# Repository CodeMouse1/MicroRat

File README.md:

# MicroRat: Eine technische Dokumentation

<div align="center">

<div align="left">

Dieses Repository dokumentiert und bündelt das Projekt MicroRat – eine an der Micromouse orientierte Plattform für Studierenden der BHT.
Es stellt ein vollständiges Paket aus Hardware und Software-Komponenten bereit und soll als Grundlage für eigene Projekte, Experimente und Weiterentwicklungen dienen.
<div align="center">
	
<div align="left">
<br>
Wenn der Begriff einer Micromouse unbekannt ist findet man unter diesem Link ein Erläuterungsvideo:
[▶️](https://www.youtube.com/watch?v=ZMQbHMgK2rw)
<br>

## Technische Beschreibung
Micromouse ist ein internationaler Robotik-Wettbewerb, bei dem kleine, autonome Roboter ein Labyrinth selbstständig erkunden und den schnellsten Weg zum Ziel finden müssen.
Die Fahrzeuge agieren vollkommen ohne externe Hilfe und entscheiden selbstständig, wie sie Hindernisse und Wände erkennen.

_Die MicroRat soll als Einstieg in diese Thematik dienen._

**Hardware Umsetzung**

Das Aussehen einer Micromouse hängt stark vom jeweiligen Erbauer ab. Die MicroRat ist bewusst so gestaltet, dass sie grundlegende Funktionen mit einfacher Benutzbarkeit und Programmierbarkeit kombiniert.
Zur Umgebungserfassung kommen folgende Sensoren zum Einsatz:
###### Sensorik
- SHARP Infrarot-Sensoren, jeweils im 90°-Winkel senkrecht zu den Wänden montiert
- HC-SR04 Ultraschall-Sensor an der Vorderseite

###### Antrieb
- DC-Motoren mit Encodern für Antrieb und Drehzahlerfassung 

###### Stromversorgung
- 2s1p Li-Ion Akkupack für stabile Energieversorgung  

###### Steuerung & Schnittstellen

- XMC-1402 Mikrocontroller, programmierbar über Debug-Connector
- UART Schnittstelle zur Ausgabe der Sensordaten 

<div align="center">

Hier ein Link zu einer 3D Ansicht: [3D-Modell](https://a360.co/3VB2RBQ)
<div align="left">
<br>

**Software-Architektur**

Die MicroRat wird über den XMC-1402 Mikrocontroller gesteuert, der Sensoren ausliest, Motoren ansteuert und die Labyrinthnavigation übernimmt.

###### Entwicklungsumgebung
- **Sprache:** C
- **IDE:** DAVE™ 
- **Debugging:** Über den Debug-Connector des XMC4500

###### Hauptfunktionen
- **Sensordaten-Auswertung:** IR- und Ultraschallsensor erkennen Wände und Hindernisse
- **Motorsteuerung:** Drehzahlgeregelte Ansteuerung der DC-Motoren mittels PD-Regler
- **Labyrinth-Algorithmus:**
	- Wandfolger (links/rechts), kartografiert
	- Floodfill, Optimierung des schnellsten Weges zum Ziel
- **Kommunikation:** Sensordaten über UART für Debugging & Logging
<div align="center">

<div align="left">

## Verwendung von KiCad 8.0
<div align="center">
	
<div align="left">
Für dieses Projekt haben wir KiCad 8.0 gewählt aus folgenden Gründen:
<br/><br/>

- **Fortschrittliche Funktionen:** Bietet erweiterte Tools für Schaltplanerstellung und Leiterplattendesign.
- **Open-Source-Software:** Kostenfrei und kontinuierlich verbessert durch eine große Community.
- **Plattformübergreifende Unterstützung:** Ermöglicht nahtlose Zusammenarbeit unabhängig vom Betriebssystem.

- **Kompatibilität und Exportmöglichkeiten:** Unterstützt viele Dateiformate und erleichtert die Integration mit anderen Tools.

Für eine grundlegende Einführung in KiCad bitte dieser Ratte folgen: [🐀](https://docs.kicad.org/)

## Anleitung

### Dave IDE 
<div align="center">
	
<div align="left">
<br>

DAVE IDE (Digital Application Virtual Engineering) ist eine benutzerfreundliche Entwicklungsumgebung für Mikrocontroller und eingebettete Systeme. Sie bietet Programmierung, Debugging und Analyse in einer Plattform.

###### Hauptfunktionen:

- **Projektverwaltung:** Projekte erstellen, importieren und konfigurieren.
- **Code-Editor:** Syntax-Highlighting, App-Help und Fehlererkennung.
- **Debugging:** Breakpoints setzen, Schritt-für-Schritt-Debugging, Variablen überwachen.

##### Erste Schritte mit DAVE IDE
- **Installation:**[⬇️](https://softwaretools.infineon.com/tools/com.ifx.tb.tool.daveide)
- **Projekt importieren:** Datei → Importieren → ZIP auswählen.

### Micromouse Simulator
<div align="center">
	
<div align="left">
<br>
Zum einfachen Testen und Erproben von Micromouse-Software ohne physische Hardware wird die Nutzung des MMS-Simulators empfohlen, mit dem Labyrinthe virtuell erstellt und Algorithmen sicher ausprobiert werden können: [Micromouse Simulator](https://github.com/mackorone/mms)

## Lizenzinformationen
Dieses Projekt ist Lizensiert unter der CC 4.0 Lizenz
https://creativecommons.org/licenses/by/4.0/

## Mitwirken
Wir freuen uns auf eure Erweiterungen! Wenn du an diesem Projekt mitarbeiten möchtest, folge bitte diesen Schritten:

1. **Fork dieses Repository**: Klicke oben rechts auf die Schaltfläche "Fork", um eine Kopie des Repositories in deinem GitLab-Konto zu erstellen.

2. **Clone das Forked Repository**: Klone dein geforktes Repository auf deinen lokalen Rechner.
    ```bash
    git clone https://github.com/dein-username/dein-repository.git
    ```

3. **Erstelle einen neuen Branch**: Erstelle einen neuen Branch für deine Arbeit.
    ```bash
    git checkout -b mein-neuer-branch
    ```

4. **Nimm deine Änderungen vor**: Führe die gewünschten Änderungen durch und committe sie.
    ```bash
    git add .
    git commit -m "Beschreibe deine Änderungen"
    ```

5. **Push deine Änderungen**: Push deine Änderungen zu deinem Fork.
    ```bash
    git push origin mein-neuer-branch
    ```

6. **Erstelle einen Pull Request**: Gehe zu deinem geforkten Repository auf GitLab und klicke auf die Schaltfläche "New Pull Request", um deine Änderungen zur Überprüfung einzureichen.

## Entwickler

Hardware & Software: Marcus Stake Alvarado

Ursprüngliches Hardware-Design: Nico Hinrichs

Ansprechprofessor: Prof. Dipl.-Ing. Koshan Mahdi

<div align="center">

**Viel Spaß mit der MicroRat**

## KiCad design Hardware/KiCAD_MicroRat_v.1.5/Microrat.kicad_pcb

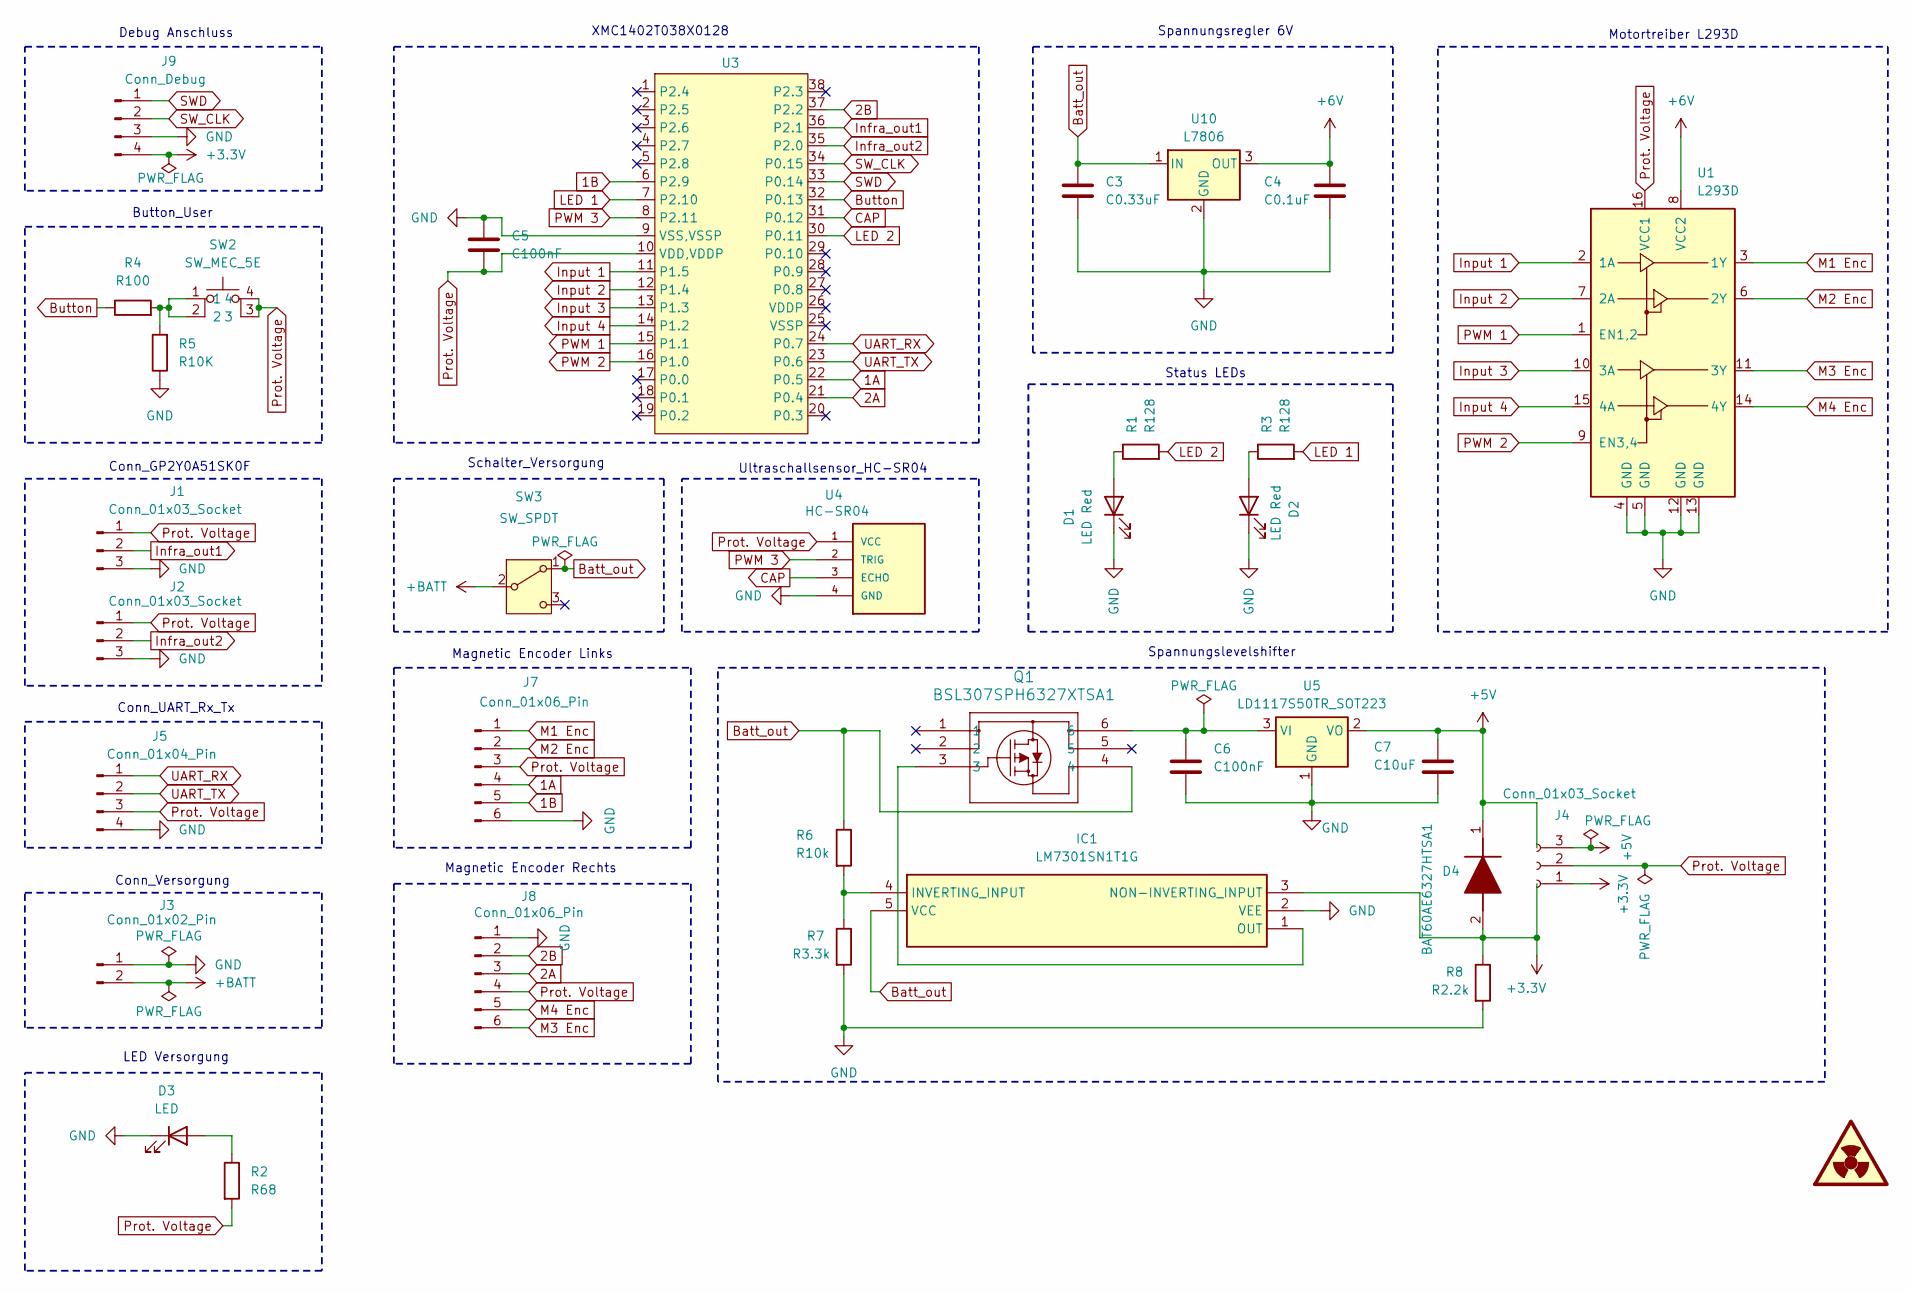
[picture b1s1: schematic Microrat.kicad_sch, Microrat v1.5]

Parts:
C3: C0.33uF; C_0805_2012Metric_Pad1.18x1.45mm_HandSolder
C4: C0.1uF; C_0805_2012Metric_Pad1.18x1.45mm_HandSolder
C5, C6: C100nF; C_0805_2012Metric_Pad1.18x1.45mm_HandSolder
C7: C10uF; C_0805_2012Metric_Pad1.18x1.45mm_HandSolder
D1, D2: LED Red; LEDC1608X80N
D3: LED; LEDC1608X80N
D4: BAT60AE6327HTSA1; SOD2513X110N; Mouser Part Number 726-BAT60AE6327HTSA1
IC1: LM7301SN1T1G; Manufacturer_Part_Number LM7301SN1T1G; Mouser Part Number 863-LM7301SN1T1G
J1, J2: Conn_01x03_Socket; SolderWire-0.1sqmm_1x03_P3.6mm_D0.4mm_OD1mm
J3: Conn_01x02_Pin; SolderWire-2.5sqmm_1x02_P7.2mm_D2.4mm_OD3.6mm
J4: Conn_01x03_Socket; PinHeader_1x03_P2.54mm_Vertical
J5: Conn_01x04_Pin; PinHeader_1x04_P2.54mm_Vertical
J7, J8: Conn_01x06_Pin; SolderWire-0.1sqmm_1x06_P3.6mm_D0.4mm_OD1mm
J9: Conn_Debug; PinHeader_1x04_P2.54mm_Vertical
Q1: BSL307SPH6327XTSA1; PG-TSOP-6-1_INF
R1, R3: R128; R_0805_2012Metric_Pad1.20x1.40mm_HandSolder
R2: R68; R_0805_2012Metric_Pad1.20x1.40mm_HandSolder
R4: R100; R_0805_2012Metric_Pad1.20x1.40mm_HandSolder
R5: R10K; R_0805_2012Metric_Pad1.20x1.40mm_HandSolder
R6: R10k; R_0805_2012Metric_Pad1.20x1.40mm_HandSolder
R7: R3.3k; R_0805_2012Metric_Pad1.20x1.40mm_HandSolder
R8: R2.2k; R_0805_2012Metric_Pad1.20x1.40mm_HandSolder
SW2: SW_MEC_5E; SW_PUSH_6mm_H4.3mm
SW3: SW_SPDT; Schiebeschalter
U1: L293D; DIP-16_W7.62mm
U3: SOP50P640X120-38N
U4: HC-SR04; XCVR_HC-SR04
U5: LD1117S50TR_SOT223; SOT-223-3_TabPin2
U10: L7806; TO-220-3_Horizontal_TabDown

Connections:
1A: J7.4, U3.22 (P0.5)
1B: J7.5, U3.6 (P2.9)
2A: J8.3, U3.21 (P0.4)
2B: J8.2, U3.37 (P2.2)
+3.3V: D4.2 (A), IC1.3 (NON-INVERTING_INPUT), J4.1, J9.4, R8.1
+5V: C7.1, D4.1 (K), J4.3, U5.2 (VO)
+6V: C4.1, U1.8 (VCC2), U10.3 (OUT)
+BATT: J3.2, SW3.2 (B)
Batt_out: C3.1, IC1.5 (VCC), Q1.4, R6.1, SW3.1 (A), U10.1 (IN)
Button: R4.1, U3.32 (P0.13)
CAP: U3.31 (P0.12), U4.3 (ECHO)
GND: C3.2, C4.2, C5.1, C6.2, C7.2, D1.1 (K), D2.1 (K), D3.1 (K), IC1.2 (VEE), J1.3, J2.3, J3.1, J5.4, J7.6, J8.1, J9.3, R5.1, R7.2, R8.2, U1.4 (GND), U1.5 (GND), U1.12 (GND), U1.13 (GND), U3.9 (VSS,VSSP), U4.4 (GND), U5.1 (GND), U10.2 (GND)
Infra_out1: J1.2, U3.36 (P2.1)
Infra_out2: J2.2, U3.35 (P2.0)
Input 1: U1.2 (1A), U3.11 (P1.5)
Input 2: U1.7 (2A), U3.12 (P1.4)
Input 3: U1.10 (3A), U3.13 (P1.3)
Input 4: U1.15 (4A), U3.14 (P1.2)
LED 1: R3.2, U3.7 (P2.10)
LED 2: R1.2, U3.30 (P0.11)
M1 Enc: J7.1, U1.3 (1Y)
M2 Enc: J7.2, U1.6 (2Y)
M3 Enc: J8.6, U1.11 (3Y)
M4 Enc: J8.5, U1.14 (4Y)
unnamed: D1.2 (A), R1.1
unnamed: D2.2 (A), R3.1
unnamed: D3.2 (A), R2.1
unnamed: IC1.4 (INVERTING_INPUT), R6.2, R7.1
unnamed: IC1.1 (OUT), Q1.3
unnamed: R4.2, R5.2, SW2.1, SW2.2
unnamed: C6.1, Q1.6, U5.3 (VI)
PWM 1: U1.1 (EN1,2), U3.15 (P1.1)
PWM 2: U1.9 (EN3,4), U3.16 (P1.0)
PWM 3: U3.8 (P2.11), U4.2 (TRIG)
Prot. Voltage: C5.2, J1.1, J2.1, J4.2, J5.3, J7.3, J8.4, R2.2, SW2.3, SW2.4, U1.16 (VCC1), U3.10 (VDD,VDDP), U4.1 (VCC)
SWD: J9.1, U3.33 (P0.14)
SW_CLK: J9.2, U3.34 (P0.15)
UART_RX: J5.1, U3.24 (P0.7)
UART_TX: J5.2, U3.23 (P0.6)

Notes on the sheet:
Magnetic Encoder Rechts
Spannungslevelshifter
XMC1402T038X0128
Conn_Versorgung
LED Versorgung
Status LEDs
Schalter_Versorgung
Conn_GP2Y0A51SK0F
Spannungsregler 6V
Conn_UART_Rx_Tx
Ultraschallsensor_HC-SR04
Debug Anschluss
Magnetic Encoder Links
Button_User
Motortreiber L293D

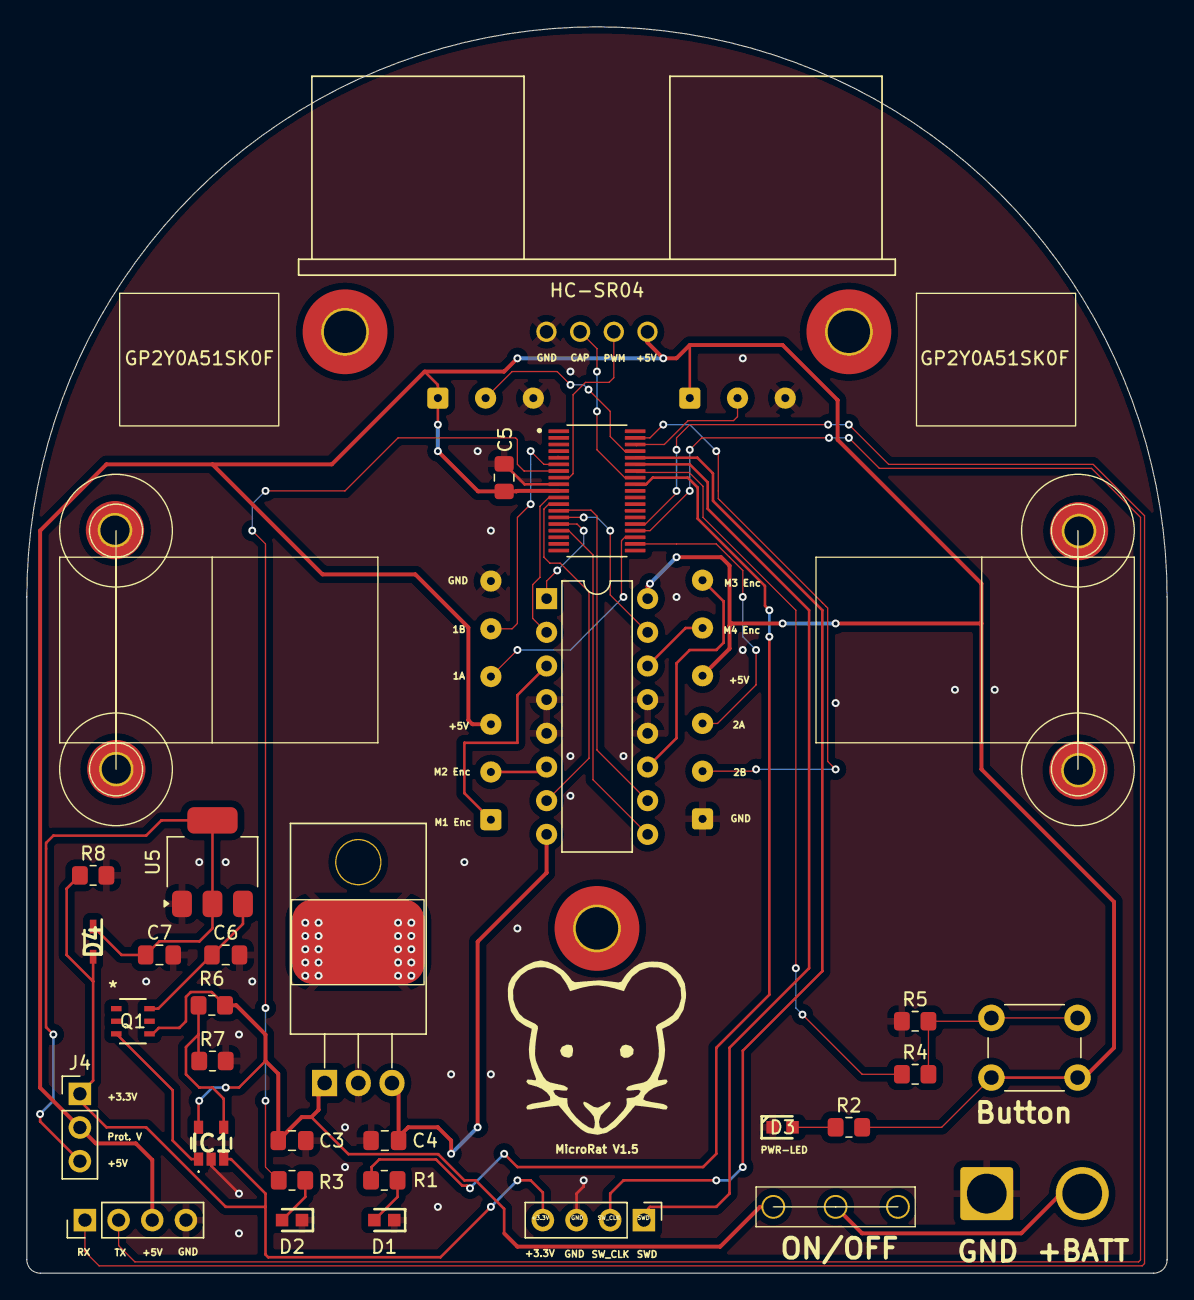
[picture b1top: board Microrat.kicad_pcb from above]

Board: 2 copper layers, 86.0 x 94.0 mm, 38 parts (0 on the bottom side), 39 nets.

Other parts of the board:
GP2Y0A51SK0F, GP2Y0A51SK0F#2: Sharp
Motor: Motor_Bracket
Motor#2: Motor_Bracket

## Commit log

2024-04-29 KiCad_pcb
2024-04-29 KiCAD_Folder
2024-04-29 Backups
2024-04-29 Stückliste & KiCAD Modelle
2024-05-02 Stückliste_02.05.24
2024-05-02 Updated version is up
2024-05-02 IR_Sharp_import
2024-05-02 XMC1402_sym
2024-05-04 änderung huhu
2024-05-04 Bild weg RIP Maus
2024-05-15 LDO Motor
2024-05-15 Schematic aktuell
2024-05-22 neue Schematic
2024-05-22 XMC neue Flags
2024-05-22 neuste Änderungen
2024-05-22 Debug
2024-05-22 neue Änderungen
2024-05-22 neues Render
2024-05-22 Final Heute
2024-05-30 Upload New File
2024-06-02 Letzter Stand KiCAD
2024-06-02 alter Stand geloescht
2024-06-02 Bilder,Fertigungsdaten,3D hinzugefügt
2024-06-02 Restdateien gelöscht
2024-06-02 MicroRat DAVE Projekt zum starten
2024-06-02 Bessere Struktur
2024-07-14 Code erweitert
2024-07-17 aktuell
2024-10-27 Replace Teilliste.xlsx
2025-04-18 Removed .settings folder from version control
2025-04-18 test
2025-04-18 Bachelorarbeit upload
2025-04-20 update BA
2025-04-23 neue Software
2025-04-25 neue Funktionen
2025-05-20 Maze Visualliser, Map & State Machine
2025-05-26 MicroRat_Wallfollower
2025-05-27 messy floodfill
2025-05-27 improved MazeVisual, tidy code & more
2025-06-02 Änderungen für Meeting
2025-06-07 BA update
2025-06-12 neues pcb
2025-06-18 Perform Diagnostic
2025-06-18 clean Architecture
2025-06-19 neues
2025-06-23 Validierung der Anforderungen
2025-06-27 last update
2025-06-27 Add new file
2025-06-27 Edit README
2025-06-28 aktuelle Links
2025-07-27 cleaning
2025-07-27 clean
2025-07-27 3D Modelle hinzugefügt für 3D Viewer
2025-07-27 KiCAD Dateien in einem Ordner
2025-07-27 Aufgeräumt: unnötige Dateien gelöscht und Ordnerstruktur bereinigt
2025-07-27 delete
2025-07-27 Finale Codeversion v1.0
2025-07-27 Ordner erstellt für source code
2025-07-27 Ordner erstellt für Bilder und Videos
2025-07-27 Aufgeräumt
2025-09-26 letzter push für v1.5
2025-09-26 added DAVE Projekt als ZIP, mit 1.5 Änderungen
2025-09-26 Rename
2025-09-28 Edit README.md
2025-09-28 Replace Microrat1.5.png
2025-09-28 Replace Microrat1.5Top.png
